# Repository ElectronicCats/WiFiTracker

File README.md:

# WiFiTracker

Based in the work of [zoutepopcorn](https://github.com/zoutepopcorn/hoeks.ma)

Electronic Cats invests time and resources providing this open source design, please support Electronic Cats and open-source hardware by purchasing products from Electronic Cats!

Designed by Electronic Cats.

Firmware released under an GNU AGPL v3.0 license. See the LICENSE file for more information.

Hardware released under an CERN Open Hardware Licence v1.2. See the LICENSE_HARDWARE file for more information.

Electronic Cats is a registered trademark, please do not use if you sell these PCBs.

20 Feb 2017

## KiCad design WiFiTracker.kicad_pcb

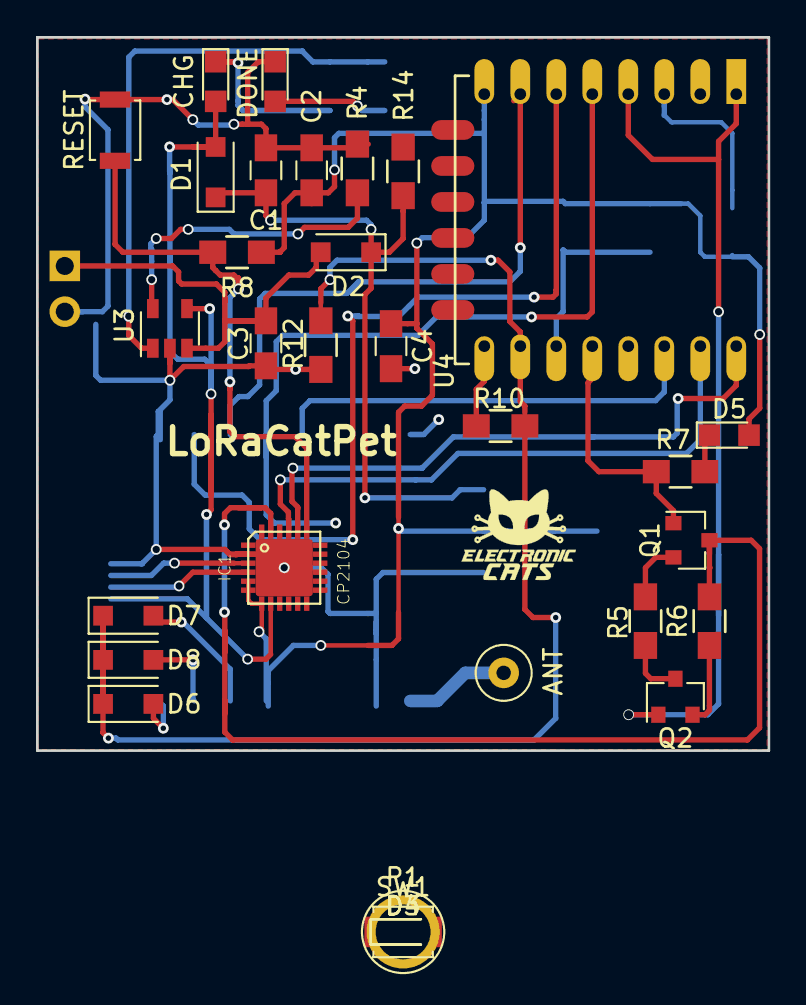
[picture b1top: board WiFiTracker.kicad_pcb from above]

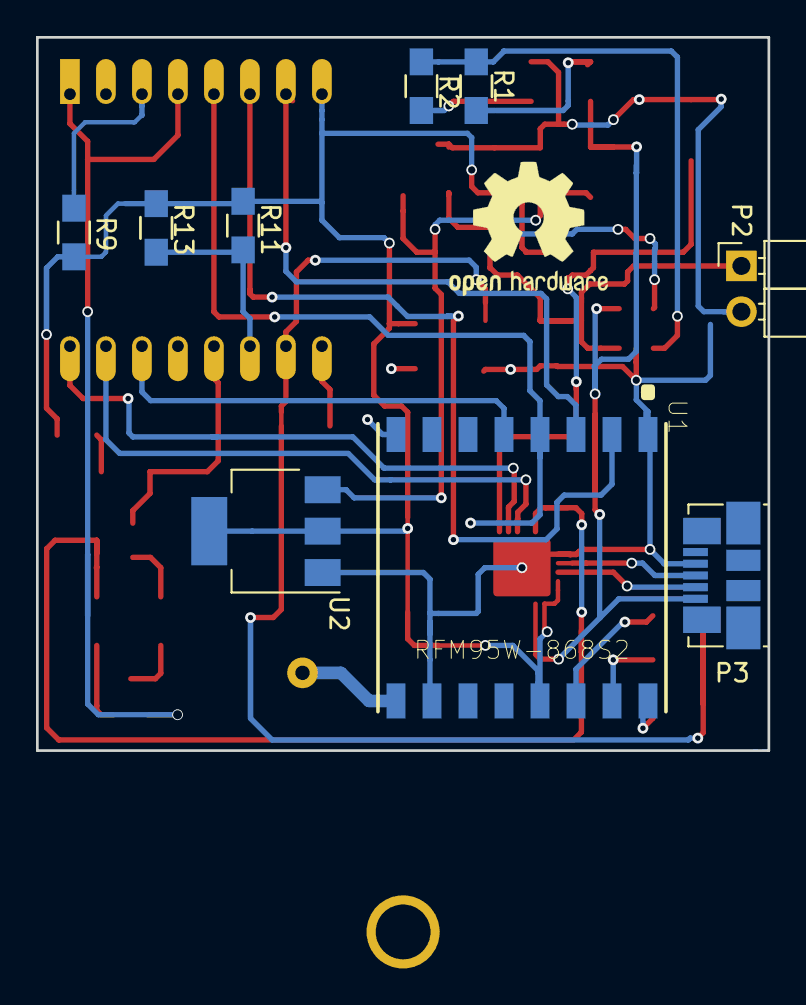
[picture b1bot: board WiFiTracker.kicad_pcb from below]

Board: 2 copper layers, 40.6 x 39.6 mm, 40 parts (9 on the bottom side), 31 nets.

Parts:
ANT: ANT; 1pin
C1, C2: 4.7uF; C_0805_HandSoldering
C3, C4: 10uF; C_0805_HandSoldering
CHG: CHG; LED_0805
D1, D2: D_Schottky; D_SOD-123F
D3: CHG; LED_0805
D4: DONE; LED_0805
D5: Led; LED_0805
D6, D7, D8: D; D_SOD-123F
DONE: DONE; LED_0805
IC1: CP2104; QFN24-PAD
P1: ANT; 1pin
P2: Battery; Pin_Header_Angled_1x02_Pitch2.54mm
P3: USB_B; USB_Micro-B_Molex_47346-0001
Q1, Q2: MMBT2222A; SOT-23
R1, R2, R7: 330R; R_0805_HandSoldering
R4, R5, R6, R8, R9, R10, R11, R12, R13, R14: 10K; R_0805_HandSoldering
RESET: SW_RESET; SW_SPST_B3U-1000P
SW1: SW_RESET; SW_SPST_B3U-1000P
U1: RFM95W-868S2; XCVR_RFM95W-868S2
U2: AP2114; SOT-223-3Lead_TabPin2
U3: MCP73831T-2ATI/OT; SOT-23-5
U4: ESP8266-12E; ESP-12E

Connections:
+3V3: C2.1, C4.1, D5.2, IC1.5, IC1.6, IC1.7, R8.1, R9.1, R11.1, R13.1, U1.13, U2.2, U4.8
+BATT: C3.1, D2.2, P2.1, U3.3
/CH_PD: R9.2, U4.3
/DIO0: D7.2, U1.14
/DIO1: D8.2, U1.15
/DIO2: D6.2, U1.16
/DTR: IC1.23, Q1.3, R6.2
/GPIO0: Q1.1, R7.1, U4.18
/GPIO2: R11.2, R13.2, U4.17
/GPIO5: U1.5, U4.20
/GPIO12: U1.2, U4.6
/GPIO13: U1.3, U4.7
/GPIO14: U1.4, U4.5
/GPIO15: D6.1, D7.1, D8.1, R10.1, R12.1, U4.16
/RESET: Q2.1, R8.2, SW1.2, U4.1, U4.4
/RTS: IC1.19, Q2.3, R5.2
/RXD: IC1.21, U4.21
/TXD: IC1.20, U4.22
GND: C1.2, C2.2, C3.2, C4.2, D4.1, DONE.1, IC1.2, IC1.TP, P2.2, P3.4, R4.2, R10.2, R12.2, RESET.1, SW1.1, U1.1, U1.8, U1.10, U2.1, U3.2, U4.15
unnamed: C1.1, D1.1, D2.1, R14.2, U2.3
unnamed: CHG.1, D3.1, R1.2
unnamed: D4.2, DONE.2, R2.2
unnamed: D5.1, R7.2
unnamed: IC1.3, P3.3
unnamed: IC1.4, P3.2
unnamed: ANT.1, P1.1, U1.9
unnamed: Q1.2, R5.1
unnamed: Q2.2, R6.1
unnamed: R1.1, R2.1, U3.1
unnamed: R4.1, U3.5
VCC: CHG.2, D1.2, D3.2, IC1.8, P3.1, U3.4

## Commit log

2017-02-20 Schematic 0.1
2017-02-20 Added gitignore
2017-02-20 updade gitignore
2017-02-20 Added javascript script
2017-02-20 Added Firmware
2017-06-08 Check PCB V0.1
2017-06-14 Added pin DIOs
2017-06-14 Add deepSleep adn Channels
2017-06-14 Update name
2017-06-14 Added Lib AP2114
2017-06-14 Arreglados los pines, se mamaron
2017-06-16 Added save fcount in eeprom
2017-07-16 Fix Reset connection
2017-08-22 Añadido lectura de voltaje VCC
    Por medio de Arduino puedes leer el voltaje de entrada
